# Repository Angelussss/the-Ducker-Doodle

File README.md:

# the-Ducker-Doodle
a custom 110% reverse exploded mechanical keyboard

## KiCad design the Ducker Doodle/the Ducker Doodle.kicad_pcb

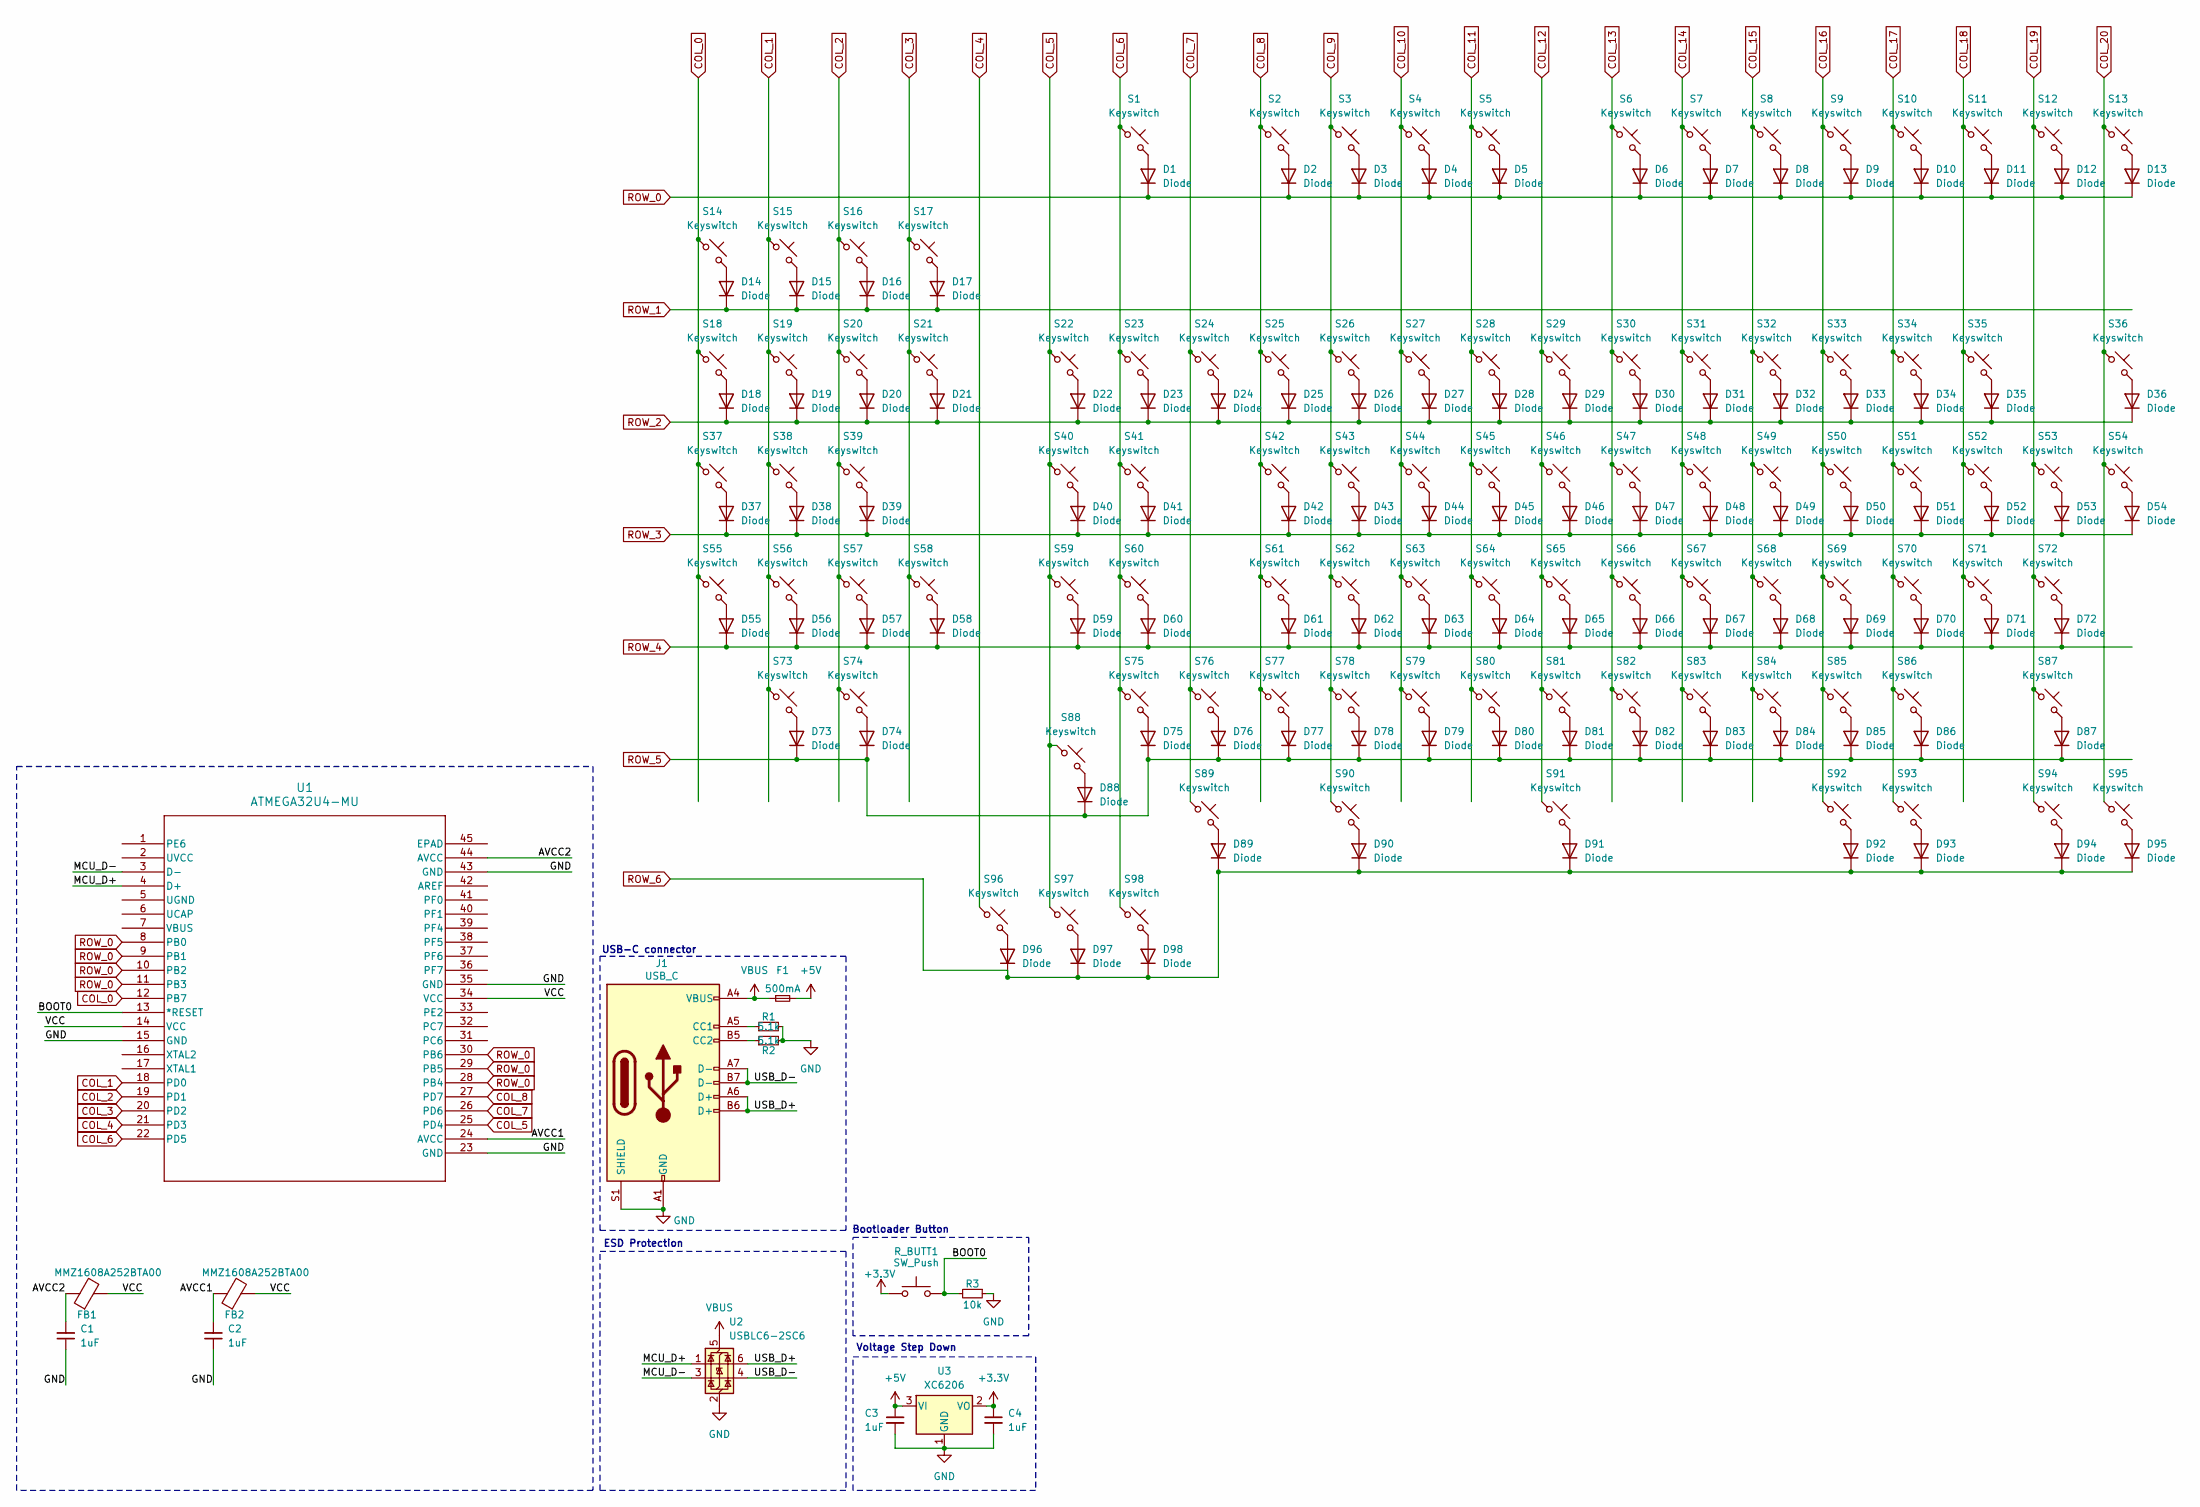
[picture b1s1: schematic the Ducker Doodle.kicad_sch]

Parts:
C1, C2: 1uF; Capacitor_0402; MPN CL05B104KB54PNC; LCSC C307331
C3, C4: 1uF; Capacitor_0402; LCSC C52923
D1, D2, D3, D4, D5, D6, D7, D8, D9, D10, D11, D12, D13, D14, D15, D16, D17, D18, D19, D20, D21, D22, D23, D24, D25, D26, D27, D28, D29, D30, D31, D32, D33, D34, D35, D36, D37, D38, D39, D40, D41, D42, D43, D44, D45, D46, D47, D48, D49, D50, D51, D52, D53, D54, D55, D56, D57, D58, D59, D60, D61, D62, D63, D64, D65, D66, D67, D68, D69, D70, D71, D72, D73, D74, D75, D76, D77, D78, D79, D80, D81, D82, D83, D84, D85, D86, D87, D88, D89, D90, D91, D92, D93, D94, D95, D96, D97, D98: Diode; Diode_SOD-123
F1: 500mA; Fuse_0603; LCSC C210357
FB1, FB2: MMZ1608A252BTA00; R_0603_1608Metric
J1: USB_C; USB_C_HRO_TYPE-C-31-M-12; LCSC C165948
R1, R2: 5.1k; R_0402_1005Metric; LCSC C25905
R3: 10k; R_0402_1005Metric; LCSC C25744
R_BUTT1: SW_Push; Button_TL3342; LCSC C115351
S1, S2, S3, S4, S5, S6, S7, S8, S9, S10, S11, S12, S13, S14, S15, S16, S17, S18, S19, S20, S21, S22, S23, S24, S25, S26, S27, S28, S29, S30, S31, S32, S33, S34, S35, S36, S37, S38, S39, S40, S41, S42, S43, S44, S45, S46, S47, S48, S49, S50, S51, S52, S53, S54, S55, S56, S57, S58, S59, S60, S61, S62, S63, S64, S65, S66, S67, S68, S69, S70, S71, S72, S73, S74, S75, S76, S77, S78, S79, S80, S81, S82, S83, S84, S85, S86, S87, S88, S89, S90, S91, S92, S93, S94, S95, S96, S97, S98: Keyswitch; MX_PCB_1.00u
U1: ATMEGA32U4-MU; 44PW_ATM
U2: USBLC6-2SC6; ESD_SOT-23-6; LCSC C2827654
U3: XC6206; Voltage_SOT-23; LCSC C5446

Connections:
+3.3V: C4.1, R_BUTT1.1, U3.2 (VO)
+5V: C3.1, F1.2, U3.3 (VI)
/AVCC1: C2.2, FB2.1, U1.24 (AVCC)
/AVCC2: C1.2, FB1.1, U1.44 (AVCC)
/BOOT0: R3.2, R_BUTT1.2, U1.13 (*RESET)
/MCU_D+: U1.4 (D+), U2.1 (I/O1)
/MCU_D-: U1.3 (D-), U2.3 (I/O2)
/USB_D+: J1.A6 (D+), J1.B6 (D+), U2.6 (I/O1)
/USB_D-: J1.A7 (D-), J1.B7 (D-), U2.4 (I/O2)
/VCC: FB1.2, FB2.2, U1.14 (VCC), U1.34 (VCC)
COL_0: S14.1, S18.1, S37.1, S55.1, U1.12 (PB7)
COL_1: S15.1, S19.1, S38.1, S56.1, S73.1, U1.18 (PD0)
COL_2: S16.1, S20.1, S39.1, S57.1, S74.1, U1.19 (PD1)
COL_3: S17.1, S21.1, S58.1, U1.20 (PD2)
COL_4: S96.1, U1.21 (PD3)
COL_5: S22.1, S40.1, S59.1, S88.1, S97.1, U1.25 (PD4)
COL_6: S1.1, S23.1, S41.1, S60.1, S75.1, S98.1, U1.22 (PD5)
COL_7: S24.1, S76.1, S89.1, U1.26 (PD6)
COL_8: S2.1, S25.1, S42.1, S61.1, S77.1, U1.27 (PD7)
COL_9: S3.1, S26.1, S43.1, S62.1, S78.1, S90.1
COL_10: S4.1, S27.1, S44.1, S63.1, S79.1
COL_11: S5.1, S28.1, S45.1, S64.1, S80.1
COL_12: S29.1, S46.1, S65.1, S81.1, S91.1
COL_13: S6.1, S30.1, S47.1, S66.1, S82.1
COL_14: S7.1, S31.1, S48.1, S67.1, S83.1
COL_15: S8.1, S32.1, S49.1, S68.1, S84.1
COL_16: S9.1, S33.1, S50.1, S69.1, S85.1, S92.1
COL_17: S10.1, S34.1, S51.1, S70.1, S86.1, S93.1
COL_18: S11.1, S35.1, S52.1, S71.1
COL_19: S12.1, S53.1, S72.1, S87.1, S94.1
COL_20: S13.1, S36.1, S54.1, S95.1
GND: C1.1, C2.1, C3.2, C4.2, J1.A1 (GND), J1.A12 (GND), J1.B1 (GND), J1.B12 (GND), J1.S1 (SHIELD), R1.2, R2.2, R3.1, U1.15 (GND), U1.23 (GND), U1.35 (GND), U1.43 (GND), U2.2 (GND), U3.1 (GND)
unnamed: D1.2 (A), S1.2
unnamed: D2.2 (A), S2.2
unnamed: D3.2 (A), S3.2
unnamed: D4.2 (A), S4.2
unnamed: D5.2 (A), S5.2
unnamed: D6.2 (A), S6.2
unnamed: D7.2 (A), S7.2
unnamed: D8.2 (A), S8.2
unnamed: D9.2 (A), S9.2
unnamed: D10.2 (A), S10.2
unnamed: D11.2 (A), S11.2
unnamed: D12.2 (A), S12.2
unnamed: D13.2 (A), S13.2
unnamed: D14.2 (A), S14.2
unnamed: D15.2 (A), S15.2
unnamed: D16.2 (A), S16.2
unnamed: D17.2 (A), S17.2
unnamed: D18.2 (A), S18.2
unnamed: D19.2 (A), S19.2
unnamed: D20.2 (A), S20.2
unnamed: D21.2 (A), S21.2
unnamed: D22.2 (A), S22.2
unnamed: D23.2 (A), S23.2
unnamed: D24.2 (A), S24.2
unnamed: D25.2 (A), S25.2
unnamed: D26.2 (A), S26.2
unnamed: D27.2 (A), S27.2
unnamed: D28.2 (A), S28.2
unnamed: D29.2 (A), S29.2
unnamed: D30.2 (A), S30.2
unnamed: D31.2 (A), S31.2
unnamed: D32.2 (A), S32.2
unnamed: D33.2 (A), S33.2
unnamed: D34.2 (A), S34.2
unnamed: D35.2 (A), S35.2
unnamed: D36.2 (A), S36.2
unnamed: D37.2 (A), S37.2
unnamed: D38.2 (A), S38.2
unnamed: D39.2 (A), S39.2
unnamed: D40.2 (A), S40.2
unnamed: D41.2 (A), S41.2
unnamed: D42.2 (A), S42.2
unnamed: D43.2 (A), S43.2
unnamed: D44.2 (A), S44.2
unnamed: D45.2 (A), S45.2
unnamed: D46.2 (A), S46.2
unnamed: D47.2 (A), S47.2
unnamed: D48.2 (A), S48.2
unnamed: D49.2 (A), S49.2
unnamed: D50.2 (A), S50.2
unnamed: D51.2 (A), S51.2
unnamed: D52.2 (A), S52.2
unnamed: D53.2 (A), S53.2
unnamed: D54.2 (A), S54.2
unnamed: D55.2 (A), S55.2
unnamed: D56.2 (A), S56.2
unnamed: D57.2 (A), S57.2
unnamed: D58.2 (A), S58.2
unnamed: D59.2 (A), S59.2
unnamed: D60.2 (A), S60.2
unnamed: D61.2 (A), S61.2
unnamed: D62.2 (A), S62.2
unnamed: D63.2 (A), S63.2
unnamed: D64.2 (A), S64.2
unnamed: D65.2 (A), S65.2
unnamed: D66.2 (A), S66.2
unnamed: D67.2 (A), S67.2
unnamed: D68.2 (A), S68.2
unnamed: D69.2 (A), S69.2
unnamed: D70.2 (A), S70.2
unnamed: D71.2 (A), S71.2
unnamed: D72.2 (A), S72.2
unnamed: D73.2 (A), S73.2
unnamed: D74.2 (A), S74.2
unnamed: D75.2 (A), S75.2
unnamed: D76.2 (A), S76.2
unnamed: D77.2 (A), S77.2
unnamed: D78.2 (A), S78.2
unnamed: D79.2 (A), S79.2
unnamed: D80.2 (A), S80.2
unnamed: D81.2 (A), S81.2
unnamed: D82.2 (A), S82.2
unnamed: D83.2 (A), S83.2
unnamed: D84.2 (A), S84.2
unnamed: D85.2 (A), S85.2
unnamed: D86.2 (A), S86.2
unnamed: D87.2 (A), S87.2
unnamed: D88.2 (A), S88.2
unnamed: D89.2 (A), S89.2
unnamed: D90.2 (A), S90.2
unnamed: D91.2 (A), S91.2
unnamed: D92.2 (A), S92.2
unnamed: D93.2 (A), S93.2
unnamed: D94.2 (A), S94.2
unnamed: D95.2 (A), S95.2
unnamed: D96.2 (A), S96.2
unnamed: D97.2 (A), S97.2
unnamed: D98.2 (A), S98.2
unnamed: J1.A5 (CC1), R1.1
unnamed: J1.B5 (CC2), R2.1
ROW_0: D1.1 (K), D2.1 (K), D3.1 (K), D4.1 (K), D5.1 (K), D6.1 (K), D7.1 (K), D8.1 (K), D9.1 (K), D10.1 (K), D11.1 (K), D12.1 (K), D13.1 (K), U1.8 (PB0), U1.9 (PB1), U1.10 (PB2), U1.11 (PB3), U1.28 (PB4), U1.29 (PB5), U1.30 (PB6)
ROW_1: D14.1 (K), D15.1 (K), D16.1 (K), D17.1 (K)
ROW_2: D18.1 (K), D19.1 (K), D20.1 (K), D21.1 (K), D22.1 (K), D23.1 (K), D24.1 (K), D25.1 (K), D26.1 (K), D27.1 (K), D28.1 (K), D29.1 (K), D30.1 (K), D31.1 (K), D32.1 (K), D33.1 (K), D34.1 (K), D35.1 (K), D36.1 (K)
ROW_3: D37.1 (K), D38.1 (K), D39.1 (K), D40.1 (K), D41.1 (K), D42.1 (K), D43.1 (K), D44.1 (K), D45.1 (K), D46.1 (K), D47.1 (K), D48.1 (K), D49.1 (K), D50.1 (K), D51.1 (K), D52.1 (K), D53.1 (K), D54.1 (K)
ROW_4: D55.1 (K), D56.1 (K), D57.1 (K), D58.1 (K), D59.1 (K), D60.1 (K), D61.1 (K), D62.1 (K), D63.1 (K), D64.1 (K), D65.1 (K), D66.1 (K), D67.1 (K), D68.1 (K), D69.1 (K), D70.1 (K), D71.1 (K), D72.1 (K)
ROW_5: D73.1 (K), D74.1 (K), D75.1 (K), D76.1 (K), D77.1 (K), D78.1 (K), D79.1 (K), D80.1 (K), D81.1 (K), D82.1 (K), D83.1 (K), D84.1 (K), D85.1 (K), D86.1 (K), D87.1 (K), D88.1 (K)
ROW_6: D89.1 (K), D90.1 (K), D91.1 (K), D92.1 (K), D93.1 (K), D94.1 (K), D95.1 (K), D96.1 (K), D97.1 (K), D98.1 (K)
VBUS: F1.1, J1.A4 (VBUS), J1.A9 (VBUS), J1.B4 (VBUS), J1.B9 (VBUS), U2.5 (VBUS)

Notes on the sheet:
ESD Protection
Voltage Step Down
Bootloader Button
USB-C connector

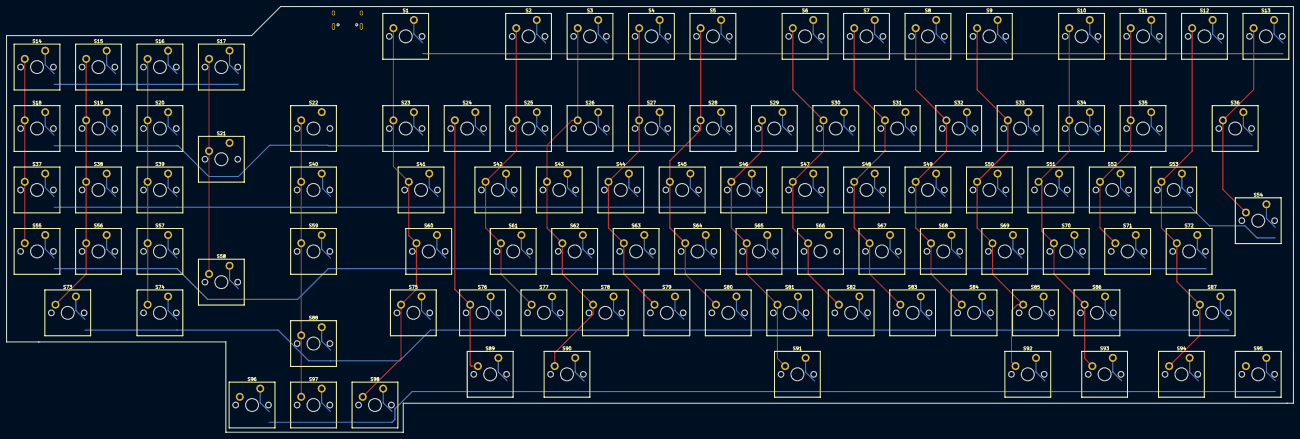
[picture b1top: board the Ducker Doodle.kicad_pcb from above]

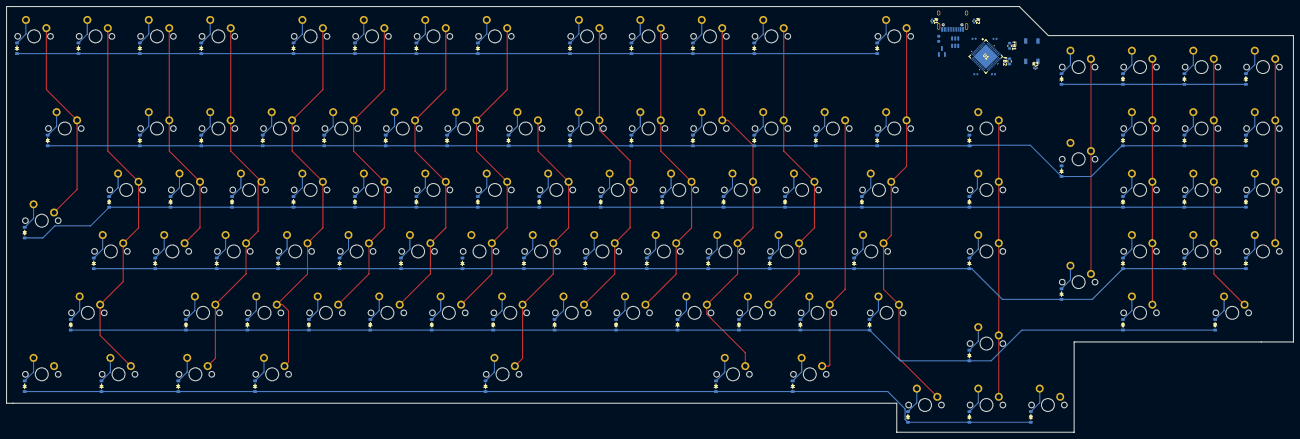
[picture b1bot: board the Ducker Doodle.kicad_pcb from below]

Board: 2 copper layers, 399.0 x 132.0 mm, 211 parts (113 on the bottom side), 140 nets.

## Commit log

2025-03-22 feat: added kicad file
2025-04-25 feat: added KLE raw
2025-04-25 feat: added wiring layout
2025-04-25 feat: added atmega32U4 libs
2025-04-25 fix: updated kicad lib-tables
2025-04-25 fix: updated readme
2025-04-25 feat: added gitignore
2025-04-25 feat: added switch matrix and usb stuff
2025-04-26 feat: added KLE json
2025-04-26 feat: keyswitch placement and basic wiring
2025-08-04 feat: updated pcb
